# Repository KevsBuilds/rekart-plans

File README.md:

# ReKart plans

**A go-kart built from a dead hoverboard.** Plans and code for ReKart, a drive-by-wire electric go-kart built from a used hoverboard for under $400 in parts. Made by Reboot Engineering, four seniors at Bartlett High School (Illinois), for PLTW Capstone Honors, 2026–27.

Project site and build log: https://kevsbuilds.github.io/HoverboardKart/

> **Status: in progress.** We're still building and testing. Nothing here is a finished, tested design yet. Files are added as each part is done, and the first full release is planned for May 2027.

## Safety first

This is a student project, not a certified product. It's a vehicle with a lithium battery and electronic-only braking. If you build from these plans, you do so at your own risk. Wear a helmet, keep a spotter on the wireless kill switch, test at walking speed first, and never charge the battery unattended.

## What's in here

| Folder | What goes in it | License |
|---|---|---|
| `firmware/` | Which hoverboard firmware we flash and the exact settings we use. Links only; no hoverboard firmware files. | MIT (our notes and settings) |
| `esp32/` | Main controller code (steering, pedals, speed modes, safety rules) and the wireless kill-switch remote. | MIT |
| `cad/` | STEP exports, DXFs for cut parts, drawing PDFs. | CC BY-SA 4.0 |
| `docs/` | Wiring diagram, parts list with prices, build steps, test data. | CC BY-SA 4.0 |

## How it works

- **Drivetrain:** the hoverboard's own hub motors and its two split control boards (one per wheel), reflashed with our fork of [Hoverboard-Firmware-Hack-Gen2.x](https://github.com/RoboDurden/Hoverboard-Firmware-Hack-Gen2.x) in UART bus mode.
- **Controls:** a steering wheel with an angle sensor and hall-effect pedals, read by an ESP32 that mixes steer and speed and sends each wheel's speed to its board over one shared UART bus (19200 baud, board IDs 0 and 1).
- **Safety:** brake overrides throttle, out-of-range pedals stop the kart, throttle must be zero at power-on, reverse only when stopped, a 10 mph cap with speed modes, and a wireless kill switch over ESP-NOW that stops the kart after 200 ms without a signal.
- **Battery:** Bioenno Power BLF-3650AS, a 36 V LiFePO4 pack (12S, 43.8 V full), sponsored by [Bioenno Power](https://www.bioennopower.com/). Charged only with a 43.8 V LiFePO4 charger.
- **Frame:** 1.5 in 6061 aluminum square tube bolted together with gusset plates. No welding.

## Licenses

- Code: MIT, see `LICENSE`.
- Plans and docs: CC BY-SA 4.0, see `LICENSE-PLANS`.
- The Gen2.x motor firmware belongs to its authors; see its repo for the license.

Not affiliated with any hoverboard brand. Product and company names belong to their owners.

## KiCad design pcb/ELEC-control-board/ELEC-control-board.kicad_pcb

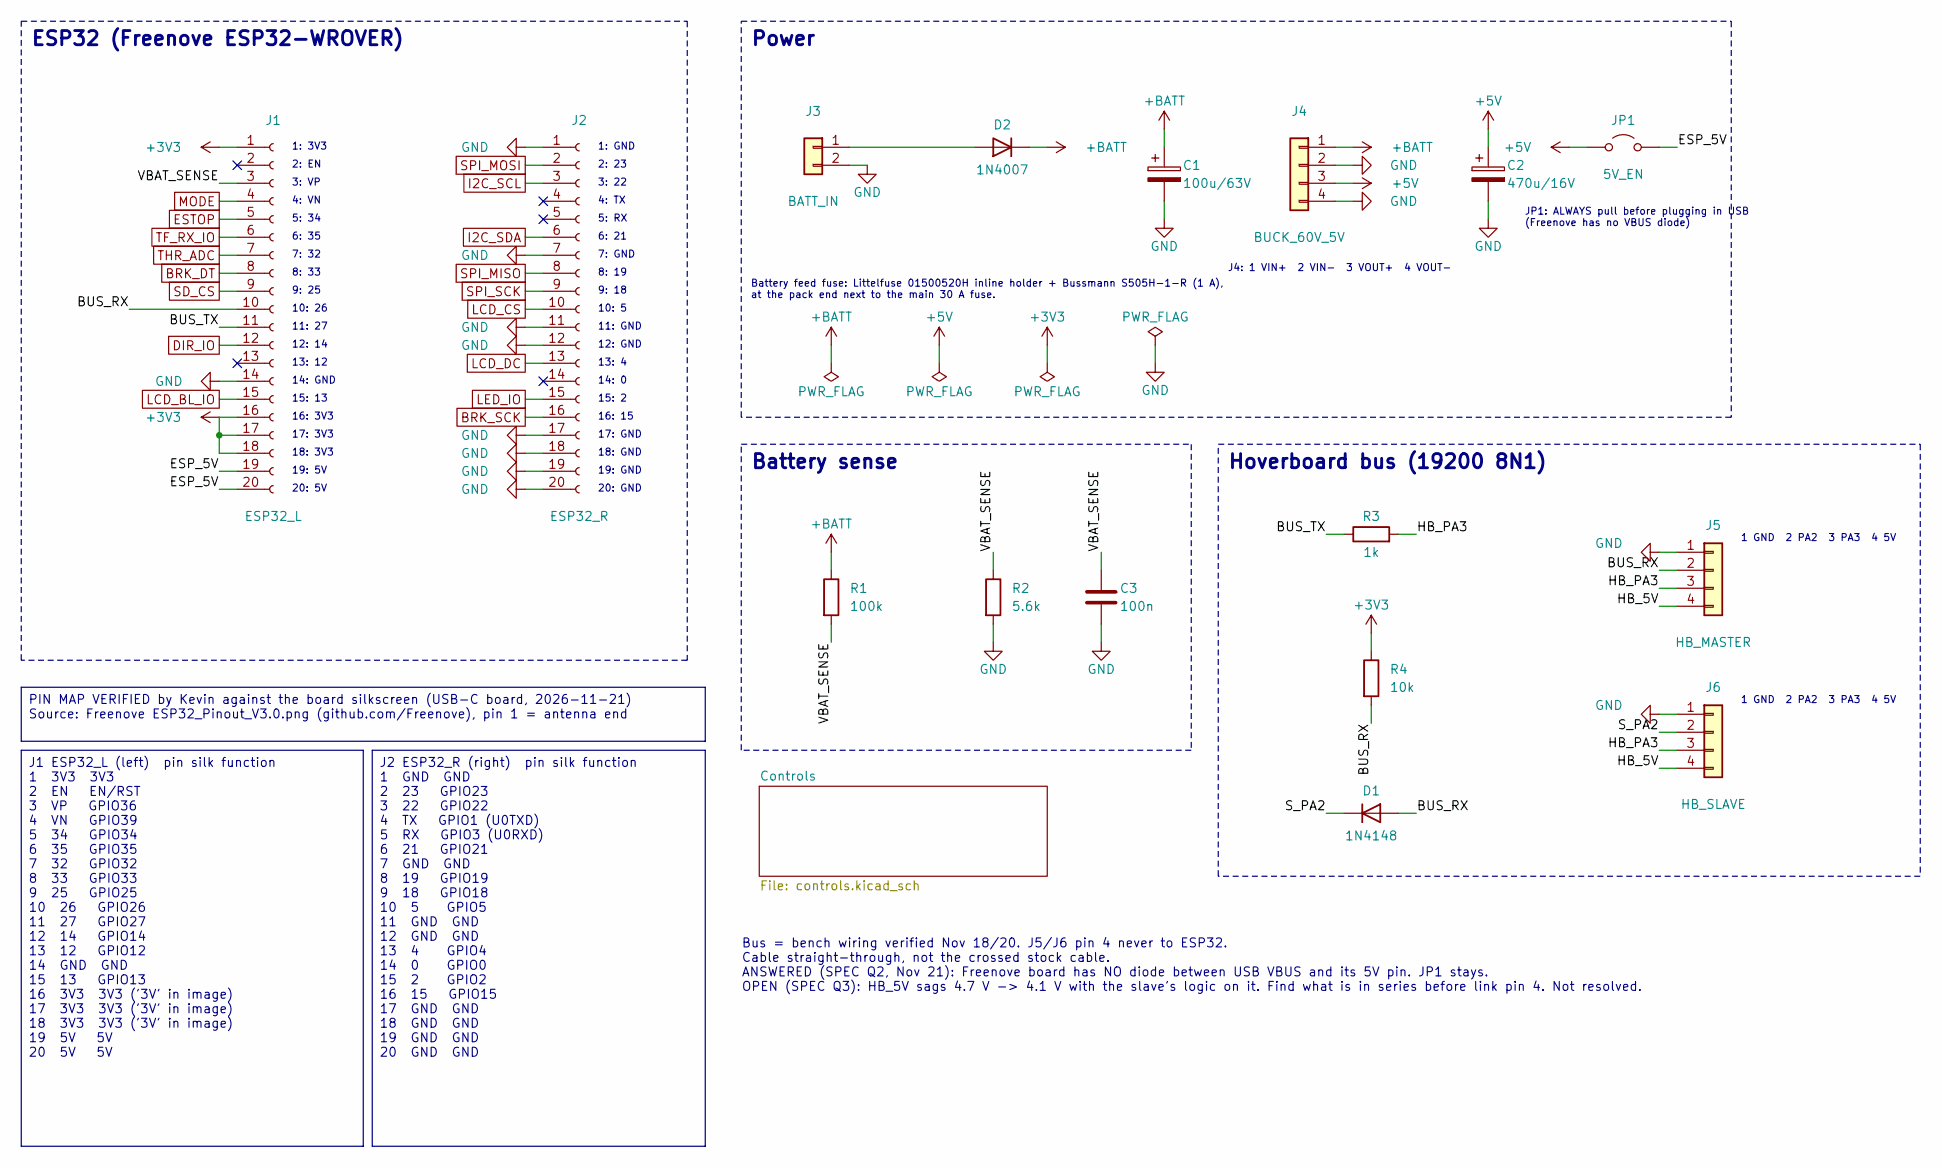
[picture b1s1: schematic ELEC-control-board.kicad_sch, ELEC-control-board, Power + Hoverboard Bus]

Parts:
C1: 100u/63V; CP_Radial_D10.0mm_P5.00mm
C2: 470u/16V; CP_Radial_D8.0mm_P3.50mm
C3: 100n; C_Disc_D5.0mm_W2.5mm_P5.00mm
D1: 1N4148; D_DO-35_SOD27_P7.62mm_Horizontal
D2: 1N4007; D_DO-41_SOD81_P10.16mm_Horizontal
J1: ESP32_L; PinSocket_1x20_P2.54mm_Vertical
J2: ESP32_R; PinSocket_1x20_P2.54mm_Vertical
J3: BATT_IN; TerminalBlock_Phoenix_MKDS-1,5-2-5.08_1x02_P5.08mm_Horizont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
J4: BUCK_60V_5V; TerminalBlock_Phoenix_MKDS-1,5-4-5.08_1x04_P5.08mm_Horizont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
J5: HB_MASTER; JST_XH_B4B-XH-A_1x04_P2.50mm_Vertical
J6: HB_SLAVE; JST_XH_B4B-XH-A_1x04_P2.50mm_Vertical
JP1: 5V_EN; PinHeader_1x02_P2.54mm_Vertical
R1: 100k; R_Axial_DIN0207_L6.3mm_D2.5mm_P10.16mm_Horizontal
R2: 5.6k; R_Axial_DIN0207_L6.3mm_D2.5mm_P10.16mm_Horizontal
R3: 1k; R_Axial_DIN0207_L6.3mm_D2.5mm_P10.16mm_Horizontal
R4: 10k; R_Axial_DIN0207_L6.3mm_D2.5mm_P10.16mm_Horizontal

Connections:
+3V3: J1.1, J1.16, J1.17, J1.18, R4.1; also elsewhere on the board
+5V: C2.1, J4.3, JP1.1 (A); also elsewhere on the board
+BATT: C1.1, D2.1 (K), J4.1, R1.1
/BUS_RX: D1.2 (A), J1.10, J5.2, R4.2
/BUS_TX: J1.11, R3.1
/ESP_5V: J1.19, J1.20, JP1.2 (B)
/HB_5V: J5.4, J6.4
/HB_PA3: J5.3, J6.3, R3.2
/S_PA2: D1.1 (K), J6.2
/VBAT_SENSE: C3.1, J1.3, R1.2, R2.1
BRK_DT: J1.8; also elsewhere on the board
BRK_SCK: J2.16; also elsewhere on the board
DIR_IO: J1.12; also elsewhere on the board
ESTOP: J1.5; also elsewhere on the board
GND: C1.2, C2.2, C3.2, J1.14, J2.1, J2.7, J2.11, J2.12, J2.17, J2.18, J2.19, J2.20, J3.2, J4.2, J4.4, J5.1, J6.1, R2.2; also elsewhere on the board
I2C_SCL: J2.3; also elsewhere on the board
I2C_SDA: J2.6; also elsewhere on the board
LCD_BL_IO: J1.15; also elsewhere on the board
LCD_CS: J2.10; also elsewhere on the board
LCD_DC: J2.13; also elsewhere on the board
LED_IO: J2.15; also elsewhere on the board
MODE: J1.4; also elsewhere on the board
unnamed: D2.2 (A), J3.1
SD_CS: J1.9; also elsewhere on the board
SPI_MISO: J2.8; also elsewhere on the board
SPI_MOSI: J2.2; also elsewhere on the board
SPI_SCK: J2.9; also elsewhere on the board
TF_RX_IO: J1.6; also elsewhere on the board
THR_ADC: J1.7; also elsewhere on the board

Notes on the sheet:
ESP32 (Freenove ESP32-WROVER)
1: 3V3
2: EN
3: VP
4: VN
5: 34
6: 35
7: 32
8: 33
9: 25
10: 26
11: 27
12: 14
13: 12
14: GND
15: 13
16: 3V3
17: 3V3
18: 3V3
19: 5V
20: 5V
1: GND
2: 23
3: 22
4: TX
5: RX
6: 21
7: GND
8: 19
9: 18
10: 5
11: GND
12: GND
13: 4
14: 0
15: 2
16: 15
17: GND
18: GND
19: GND

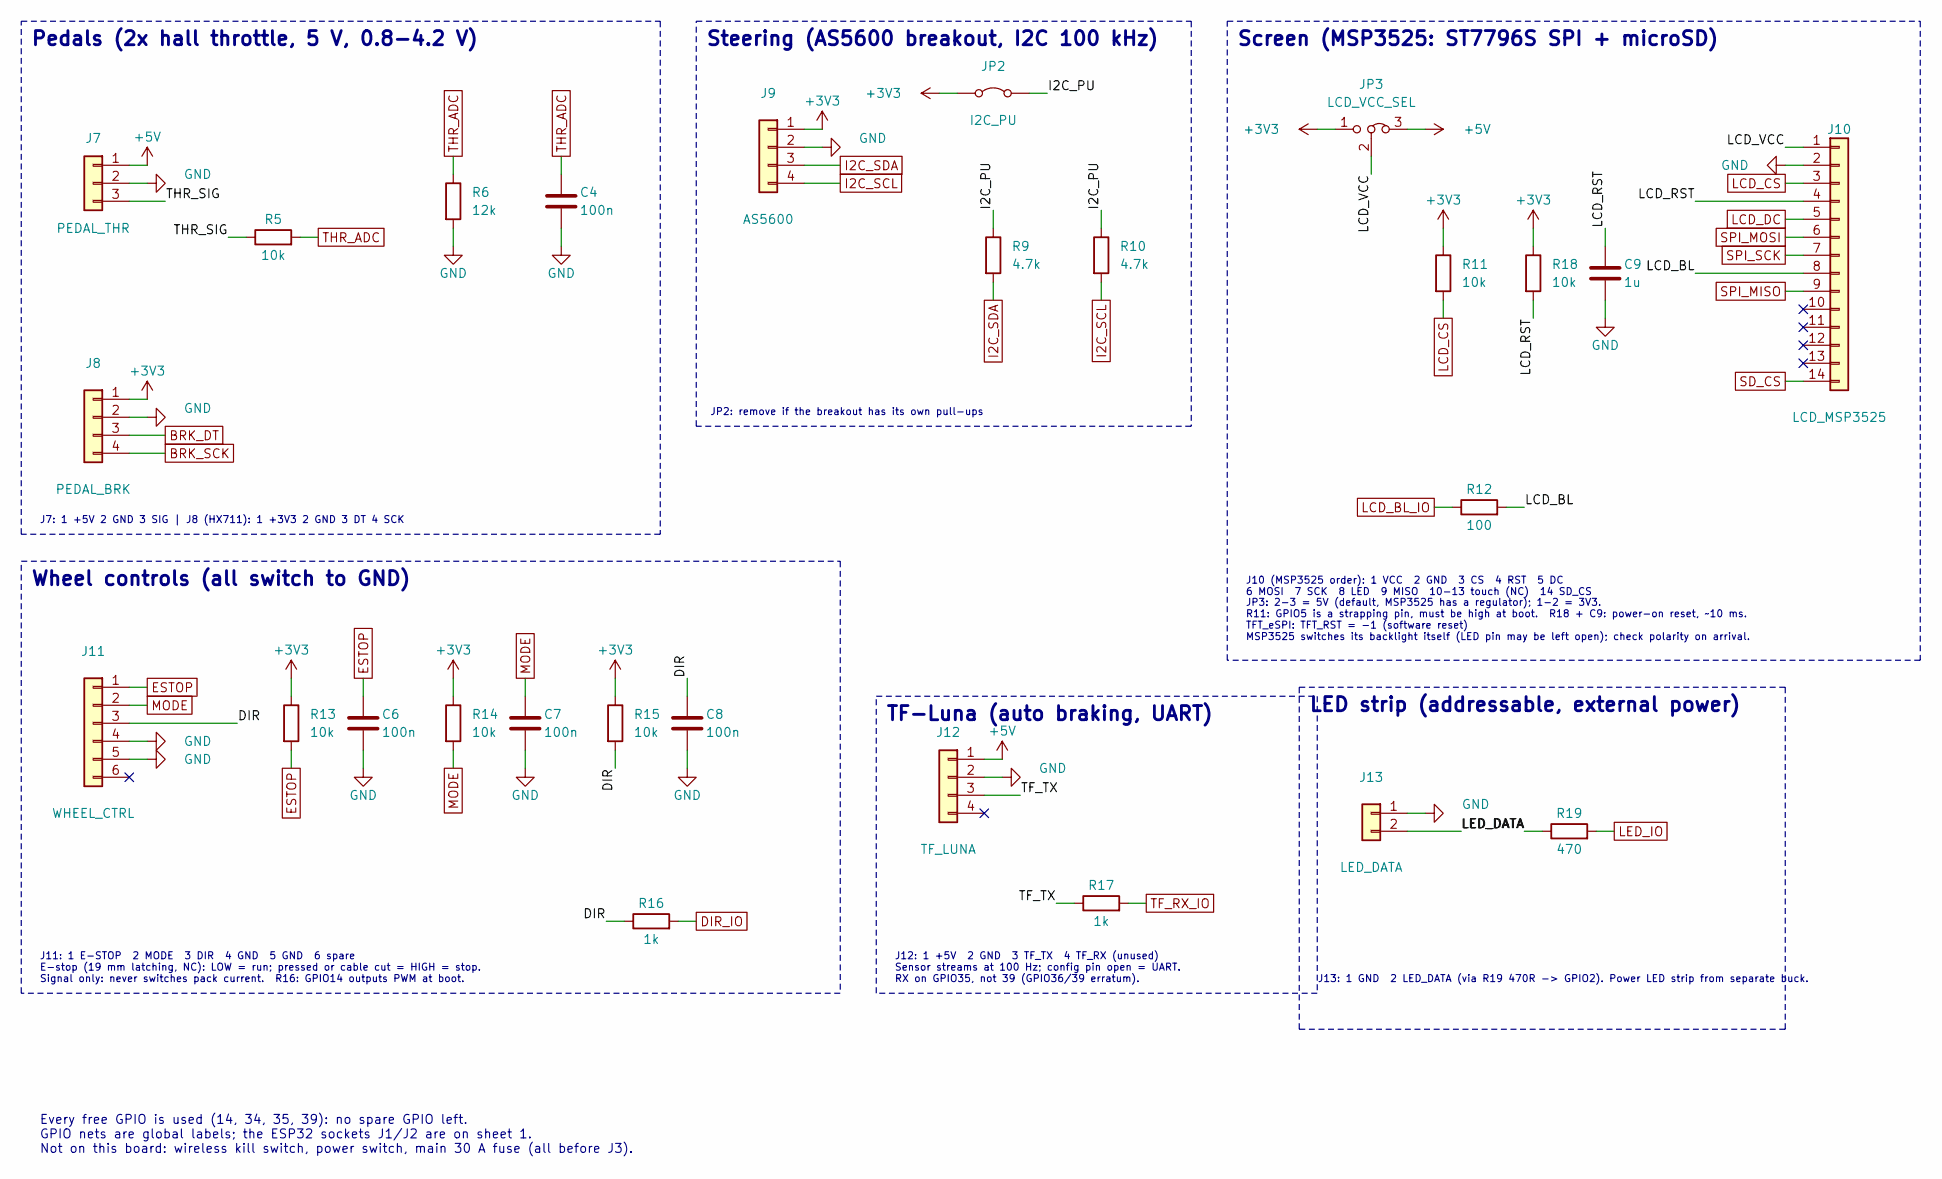
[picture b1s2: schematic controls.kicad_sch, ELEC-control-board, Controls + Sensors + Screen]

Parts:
C4, C6, C7, C8: 100n; C_Disc_D5.0mm_W2.5mm_P5.00mm
C9: 1u; C_Disc_D5.0mm_W2.5mm_P5.00mm
J7: PEDAL_THR; JST_XH_B3B-XH-A_1x03_P2.50mm_Vertical
J8: PEDAL_BRK; JST_XH_B4B-XH-A_1x04_P2.50mm_Vertical
J9: AS5600; JST_XH_B4B-XH-A_1x04_P2.50mm_Vertical
J10: LCD_MSP3525; PinHeader_1x14_P2.54mm_Vertical
J11: WHEEL_CTRL; JST_XH_B6B-XH-A_1x06_P2.50mm_Vertical
J12: TF_LUNA; JST_XH_B4B-XH-A_1x04_P2.50mm_Vertical
J13: LED_DATA; JST_XH_B2B-XH-A_1x02_P2.50mm_Vertical
JP2: I2C_PU; PinHeader_1x02_P2.54mm_Vertical
JP3: LCD_VCC_SEL; PinHeader_1x03_P2.54mm_Vertical
R5, R11, R13, R14, R15, R18: 10k; R_Axial_DIN0207_L6.3mm_D2.5mm_P10.16mm_Horizontal
R6: 12k; R_Axial_DIN0207_L6.3mm_D2.5mm_P10.16mm_Horizontal
R9, R10: 4.7k; R_Axial_DIN0207_L6.3mm_D2.5mm_P10.16mm_Horizontal
R12: 100; R_Axial_DIN0207_L6.3mm_D2.5mm_P10.16mm_Horizontal
R16, R17: 1k; R_Axial_DIN0207_L6.3mm_D2.5mm_P10.16mm_Horizontal
R19: 470; R_Axial_DIN0207_L6.3mm_D2.5mm_P10.16mm_Horizontal

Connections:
+3V3: J8.1, J9.1, JP2.1 (A), JP3.1 (A), R11.1, R13.1, R14.1, R15.1, R18.1; also elsewhere on the board
+5V: J7.1, J12.1, JP3.3 (B); also elsewhere on the board
/Controls/DIR: C8.1, J11.3, R15.2, R16.1
/Controls/I2C_PU: JP2.2 (B), R9.1, R10.1
/Controls/LCD_BL: J10.8, R12.2
/Controls/LCD_RST: C9.1, J10.4, R18.2
/Controls/LCD_VCC: J10.1, JP3.2 (C)
/Controls/LED_DATA: J13.2, R19.1
/Controls/TF_TX: J12.3, R17.1
/Controls/THR_SIG: J7.3, R5.1
BRK_DT: J8.3; also elsewhere on the board
BRK_SCK: J8.4; also elsewhere on the board
DIR_IO: R16.2; also elsewhere on the board
ESTOP: C6.1, J11.1, R13.2; also elsewhere on the board
GND: C4.2, C6.2, C7.2, C8.2, C9.2, J7.2, J8.2, J9.2, J10.2, J11.4, J11.5, J12.2, J13.1, R6.2; also elsewhere on the board
I2C_SCL: J9.4, R10.2; also elsewhere on the board
I2C_SDA: J9.3, R9.2; also elsewhere on the board
LCD_BL_IO: R12.1; also elsewhere on the board
LCD_CS: J10.3, R11.2; also elsewhere on the board
LCD_DC: J10.5; also elsewhere on the board
LED_IO: R19.2; also elsewhere on the board
MODE: C7.1, J11.2, R14.2; also elsewhere on the board
SD_CS: J10.14; also elsewhere on the board
SPI_MISO: J10.9; also elsewhere on the board
SPI_MOSI: J10.6; also elsewhere on the board
SPI_SCK: J10.7; also elsewhere on the board
TF_RX_IO: R17.2; also elsewhere on the board
THR_ADC: C4.1, R5.2, R6.1; also elsewhere on the board

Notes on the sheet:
Pedals (2x hall throttle, 5 V, 0.8-4.2 V)
J7: 1 +5V 2 GND 3 SIG | J8 (HX711): 1 +3V3 2 GND 3 DT 4 SCK
Steering (AS5600 breakout, I2C 100 kHz)
JP2: remove if the breakout has its own pull-ups
Screen (MSP3525: ST7796S SPI + microSD)
J10 (MSP3525 order): 1 VCC 2 GND 3 CS 4 RST 5 DC 6 MOSI 7 SCK 8 LED 9 MISO 10-13 touch (NC) 14 SD_CS
JP3: 2-3 = 5V (default, MSP3525 has a regulator); 1-2 = 3V3. R11: GPIO5 is a strapping pin, must be high at boot. R18 + C9: power-on reset, ~10 ms. TFT_eSPI: TFT_RST = -1 (software reset) MSP3525 switches its backlight itself (LED pin may be left open); check polarity on arrival.
Wheel controls (all switch to GND)
J11: 1 E-STOP 2 MODE 3 DIR 4 GND 5 GND 6 spare E-stop (19 mm latching, NC): LOW = run; pressed or cable cut = HIGH = stop. Signal only: never switches pack current. R16: GPIO14 outputs PWM at boot.
TF-Luna (auto braking, UART)
J12: 1 +5V 2 GND 3 TF_TX 4 TF_RX (unused) Sensor streams at 100 Hz; config pin open = UART. RX on GPIO35, not 39 (GPIO36/39 erratum).
LED strip (addressable, external power)
J13: 1 GND 2 LED_DATA (via R19 470R -> GPIO2). Power LED strip from separate buck.
Every free GPIO is used (14, 34, 35, 39): no spare GPIO left. GPIO nets are global labels; the ESP32 sockets J1/J2 are on sheet 1. Not on this board: wireless kill switch, power switch, main 30 A fuse (all before J3).

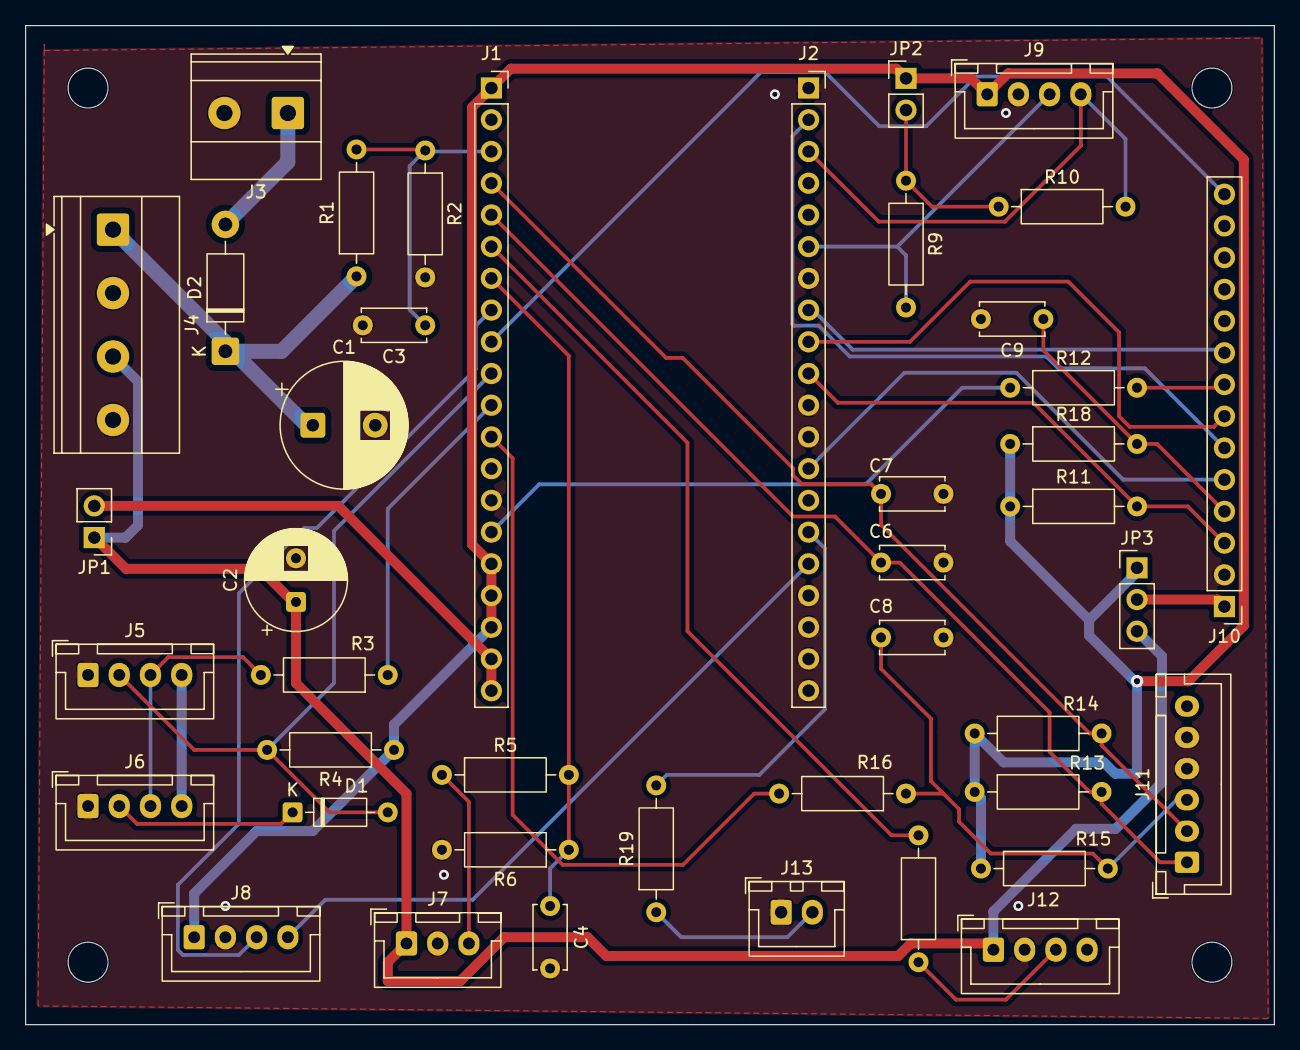
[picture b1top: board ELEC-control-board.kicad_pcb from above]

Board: 2 copper layers, 100.0 x 80.0 mm, 47 parts (0 on the bottom side), 37 nets.

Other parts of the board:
H1, H2, H3, H4: MountingHole_3.2mm_M3

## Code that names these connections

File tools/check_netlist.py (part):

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# ---- ESP32 socket pins in use (pin map verified 2026-11-21, see sheet text box) ----
ESP32_PINS = {
    "+3V3": ["J1.1", "J1.16", "J1.17", "J1.18"],      # 3V3 pins
    "ESP_5V": ["J1.19", "J1.20"],                     # 5V pins
    "GND": ["J1.14", "J2.1", "J2.7", "J2.11", "J2.12", "J2.17", "J2.18", "J2.19", "J2.20"],
    "VBAT_SENSE": ["J1.3"],                           # GPIO36 (VP)
    "BUS_RX": ["J1.10"],                              # GPIO26
    "BUS_TX": ["J1.11"],                              # GPIO27
    # sheet 2
    "MODE": ["J1.4"],                                 # GPIO39 (VN)
    "ESTOP": ["J1.5"],                                # GPIO34
    "TF_RX_IO": ["J1.6"],                             # GPIO35 (not 39: erratum)
    "THR_ADC": ["J1.7"],                              # GPIO32
    "BRK_DT": ["J1.8"],                               # GPIO33 (HX711 DOUT)
    "BRK_SCK": ["J2.16"],                             # GPIO15 (HX711 SCK)
    "SD_CS": ["J1.9"],                                # GPIO25
    "DIR_IO": ["J1.12"],                              # GPIO14
    "LCD_BL_IO": ["J1.15"],                           # GPIO13
    "SPI_MOSI": ["J2.2"],                             # GPIO23
    "I2C_SCL": ["J2.3"],                              # GPIO22
    "I2C_SDA": ["J2.6"],                              # GPIO21
    "SPI_MISO": ["J2.8"],                             # GPIO19
    "SPI_SCK": ["J2.9"],                              # GPIO18
    "LCD_CS": ["J2.10"],                              # GPIO5
    "LCD_DC": ["J2.13"],                              # GPIO4
    "LED_IO": ["J2.15"],                              # GPIO2 (addressable LED data)
}
# ESP32 pins that must stay unconnected (EN never goes to the screen: SPEC sheet 2)
ESP32_NC = ["J1.2", "J1.13", "J2.4", "J2.5", "J2.14"]
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        check(not (hb & nets.get(other, set())), f"HB_5V not joined to {other}")
    check(not ({"J5.4", "J6.4"} & set().union(*(nets.get(k, set()) for k in ("+5V", "ESP_5V", "+3V3")))),
          "J5.4/J6.4 not on +5V/ESP_5V/+3V3")
    check("D1.1" in nets.get("S_PA2", set()), "D1 pin 1 (K) on S_PA2")
    check(any(p == {"D2.2", "J3.1"} for p in nets.values()),
          "D2 anode (pin 2) directly on J3.1")
    check("D2.1" in nets.get("+BATT", set()), "D2 cathode (pin 1) on +BATT")
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    between("R16", "DIR", "DIR_IO")
    between("R17", "TF_TX", "TF_RX_IO")
    between("R19", "LED_DATA", "LED_IO")
    check("J2.15" in nets.get("LED_IO", set()), "LED_IO on GPIO2 (J2.15)")
    check(not ({"J13.1", "J13.2"} & set().union(*(nets.get(k, set()) for k in ("+5V", "ESP_5V", "+3V3")))),
          "J13 (LED_DATA) has no board power rail (+5V/ESP_5V/+3V3)")
    check("J1.6" in nets.get("TF_RX_IO", set()) and "J1.4" not in nets.get("TF_RX_IO", set()),
          "TF-Luna RX on GPIO35 (J1.6), not GPIO39 (J1.4)")
    check(not any(p.startswith(("J1.", "J2.")) for p in nets.get("LCD_RST", set())),
          "LCD_RST touches no ESP32 pin (not EN)")

    print()
    print(f"{len(fails)} failure(s)" if fails else "ALL CHECKS PASSED")
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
